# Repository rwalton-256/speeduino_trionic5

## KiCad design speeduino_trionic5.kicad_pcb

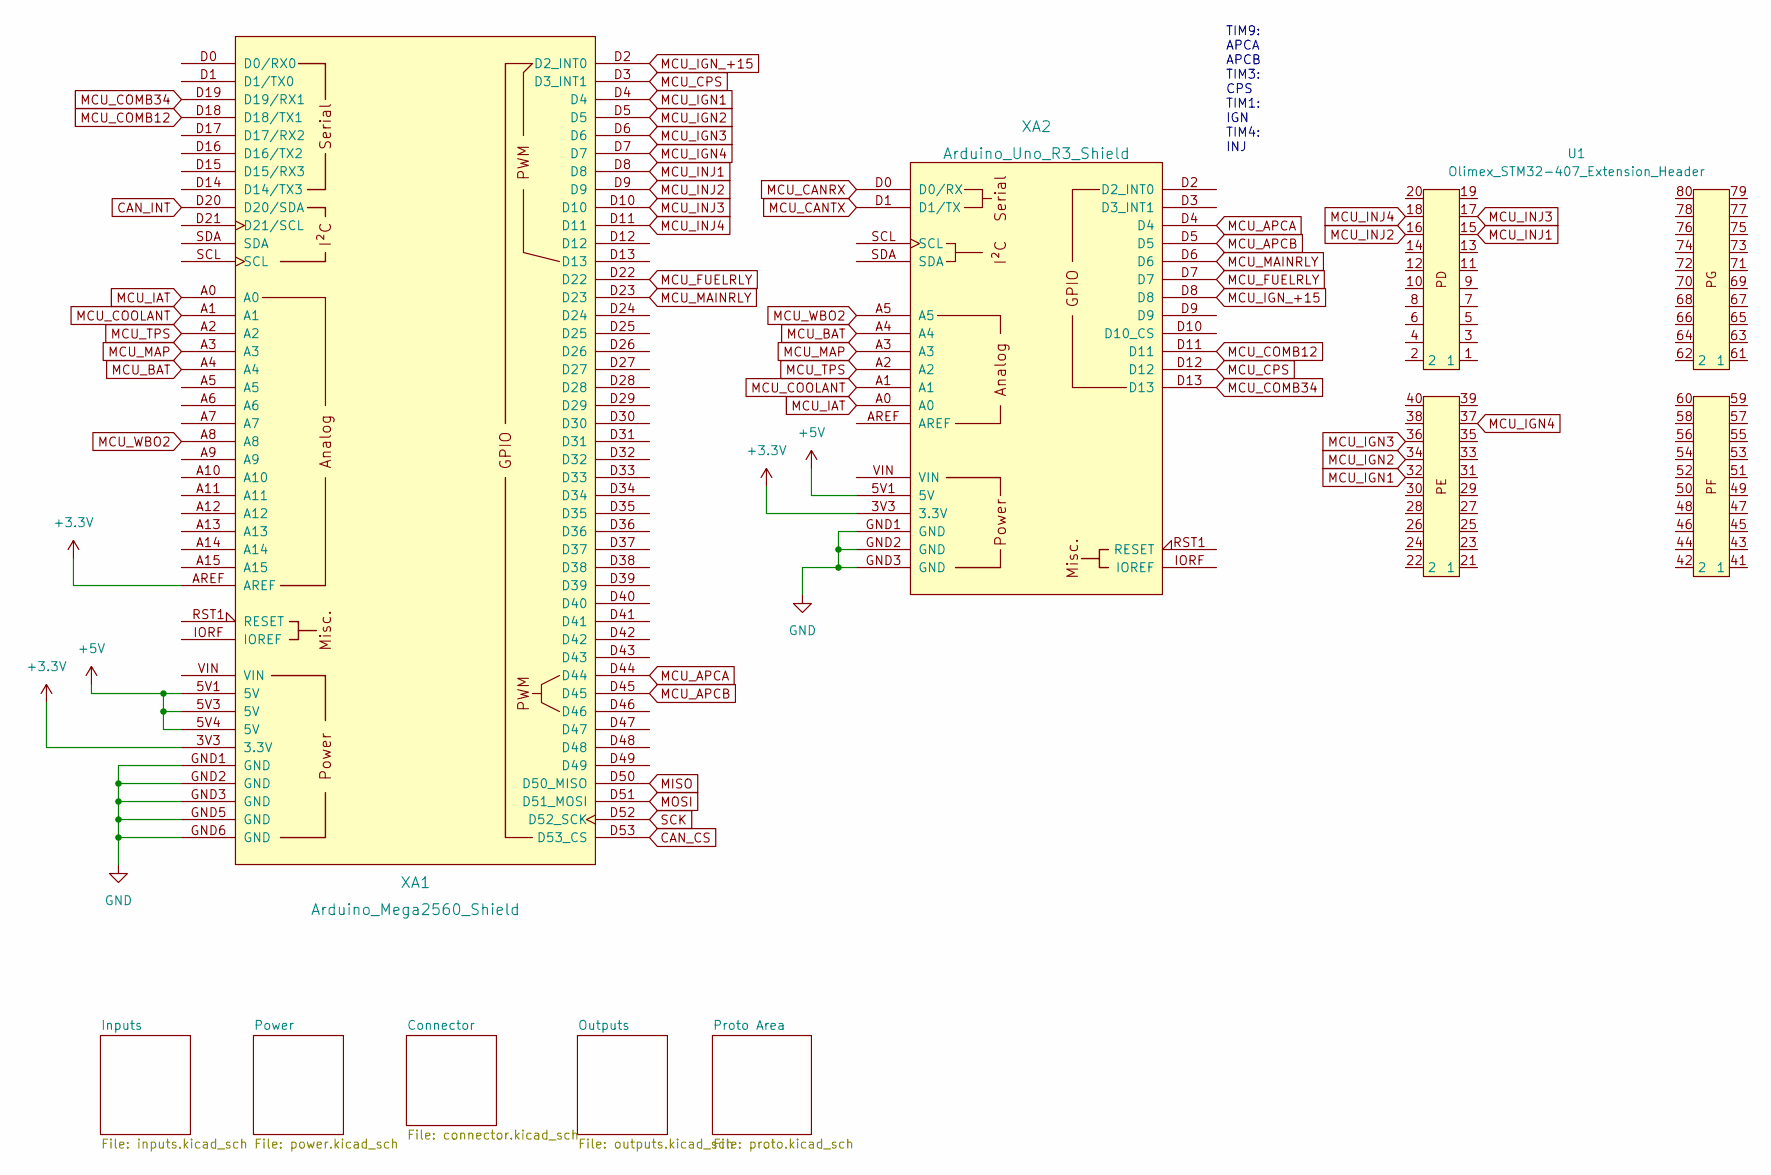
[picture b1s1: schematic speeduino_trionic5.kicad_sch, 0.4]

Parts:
U1: Olimex_STM32-407_Extension_Header; Olimex_STM32-E407_Extenstion_Header
XA1: Arduino_Mega2560_Shield
XA2: Arduino_Uno_R3_Shield

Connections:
+3.3V: XA1.3V3 (3.3V), XA1.AREF, XA2.3V3 (3.3V); also elsewhere on the board
+5V: XA1.5V1 (5V), XA1.5V3 (5V), XA1.5V4 (5V), XA2.5V1 (5V); also elsewhere on the board
CAN_CS: XA1.D53 (D53_CS); also elsewhere on the board
CAN_INT: XA1.D20 (D20/SDA); also elsewhere on the board
GND: XA1.GND1 (GND), XA1.GND2 (GND), XA1.GND3 (GND), XA1.GND5 (GND), XA1.GND6 (GND), XA2.GND1 (GND), XA2.GND2 (GND), XA2.GND3 (GND); also elsewhere on the board
MCU_APCA: XA1.D44, XA2.D4; also elsewhere on the board
MCU_APCB: XA1.D45, XA2.D5; also elsewhere on the board
MCU_BAT: XA1.A4, XA2.A4; also elsewhere on the board
MCU_CANRX: XA2.D0 (D0/RX); also elsewhere on the board
MCU_CANTX: XA2.D1 (D1/TX); also elsewhere on the board
MCU_COMB12: XA1.D18 (D18/TX1), XA2.D11; also elsewhere on the board
MCU_COMB34: XA1.D19 (D19/RX1), XA2.D13; also elsewhere on the board
MCU_COOLANT: XA1.A1, XA2.A1; also elsewhere on the board
MCU_CPS: XA1.D3 (D3_INT1), XA2.D12; also elsewhere on the board
MCU_FUELRLY: XA1.D22, XA2.D7; also elsewhere on the board
MCU_IAT: XA1.A0, XA2.A0; also elsewhere on the board
MCU_IGN1: U1.32, XA1.D4; also elsewhere on the board
MCU_IGN2: U1.34, XA1.D5; also elsewhere on the board
MCU_IGN3: U1.36, XA1.D6; also elsewhere on the board
MCU_IGN4: U1.37, XA1.D7; also elsewhere on the board
MCU_IGN_+15: XA1.D2 (D2_INT0), XA2.D8; also elsewhere on the board
MCU_INJ1: U1.15, XA1.D8; also elsewhere on the board
MCU_INJ2: U1.16, XA1.D9; also elsewhere on the board
MCU_INJ3: U1.17, XA1.D10; also elsewhere on the board
MCU_INJ4: U1.18, XA1.D11; also elsewhere on the board
MCU_MAINRLY: XA1.D23, XA2.D6; also elsewhere on the board
MCU_MAP: XA1.A3, XA2.A3; also elsewhere on the board
MCU_TPS: XA1.A2, XA2.A2; also elsewhere on the board
MCU_WBO2: XA1.A8, XA2.A5; also elsewhere on the board
MISO: XA1.D50 (D50_MISO); also elsewhere on the board
MOSI: XA1.D51 (D51_MOSI); also elsewhere on the board
SCK: XA1.D52 (D52_SCK); also elsewhere on the board

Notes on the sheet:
TIM9: APCA APCB TIM3: CPS TIM1: IGN TIM4: INJ

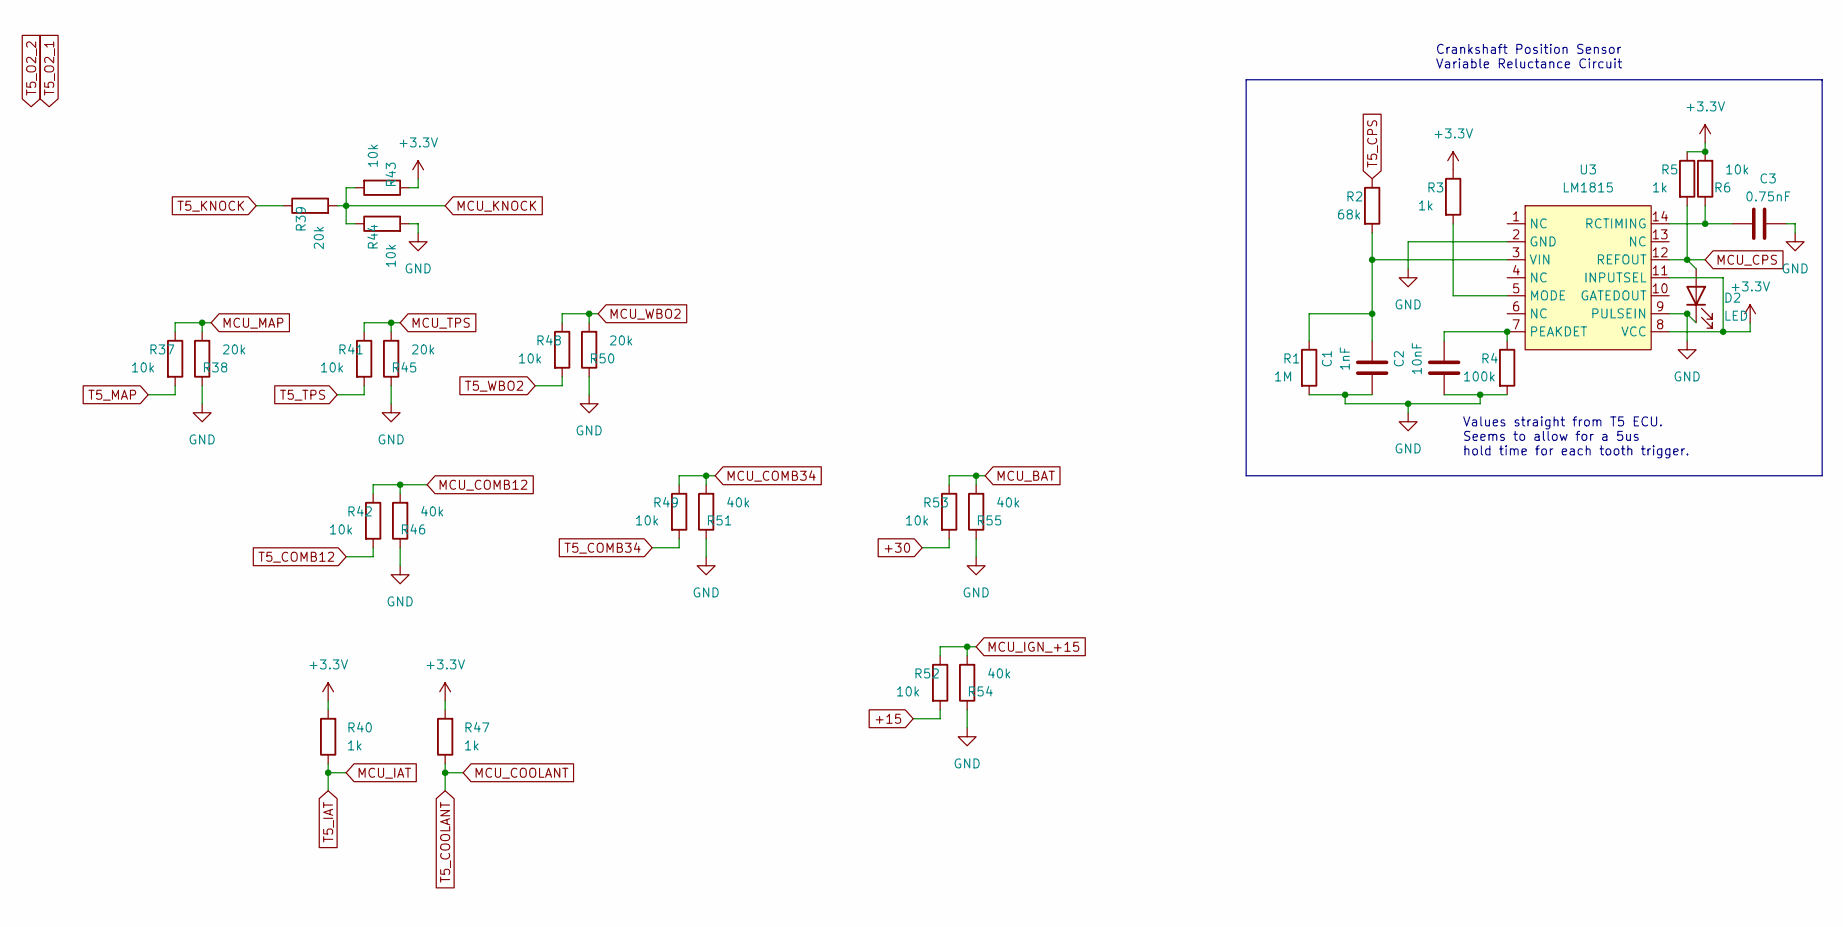
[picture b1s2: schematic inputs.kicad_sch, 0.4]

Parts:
C1: 1nF; C_0603_1608Metric; JLCPCB C296015
C2: 10nF; C_0603_1608Metric; JLCPCB C424843
C3: 0.75nF; C_0603_1608Metric; JLCPCB C576855
D2: LED; LED_0603_1608Metric; JLCPCB C84263
R1: 1M; R_0603_1608Metric; JLCPCB C188125
R2: 68k; R_0603_1608Metric; JLCPCB C2933251
R3, R5, R40, R47: 1k; R_0603_1608Metric; JLCPCB C217840
R4: 100k; R_0603_1608Metric; JLCPCB C100822
R6, R37, R41, R42, R43, R44, R48, R49, R52, R53: 10k; R_0603_1608Metric; JLCPCB C21190
R38, R39, R45, R50: 20k; R_0603_1608Metric; JLCPCB C2924194
R46, R51, R54, R55: 40k; R_0603_1608Metric; JLCPCB C706088
U3: LM1815; SOIC-14_3.9x8.7mm_P1.27mm

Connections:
+3.3V: R3.1, R5.1, R6.2, R40.2, R43.1, R47.2, U3.8 (VCC), U3.11 (INPUTSEL); also elsewhere on the board
+15: R52.2; also elsewhere on the board
+30: R53.2; also elsewhere on the board
GND: C1.1, C2.1, C3.2, D2.1 (K), R1.2, R4.2, R38.1, R44.2, R45.1, R46.1, R50.1, R51.1, R54.1, R55.1, U3.2 (GND), U3.9 (PULSEIN); also elsewhere on the board
MCU_BAT: R53.1, R55.2; also elsewhere on the board
MCU_COMB12: R42.1, R46.2; also elsewhere on the board
MCU_COMB34: R49.1, R51.2; also elsewhere on the board
MCU_COOLANT: R47.1; also elsewhere on the board
MCU_CPS: D2.2 (A), R5.2, U3.12 (REFOUT); also elsewhere on the board
MCU_IAT: R40.1; also elsewhere on the board
MCU_IGN_+15: R52.1, R54.2; also elsewhere on the board
MCU_KNOCK: R39.2, R43.2, R44.1
MCU_MAP: R37.1, R38.2; also elsewhere on the board
MCU_TPS: R41.1, R45.2; also elsewhere on the board
MCU_WBO2: R48.1, R50.2; also elsewhere on the board
unnamed: C1.2, R1.1, R2.2, U3.3 (VIN)
unnamed: C2.2, R4.1, U3.7 (PEAKDET)
unnamed: C3.1, R6.1, U3.14 (RCTIMING)
unnamed: R3.2, U3.5 (MODE)
T5_COMB12: R42.2; also elsewhere on the board
T5_COMB34: R49.2; also elsewhere on the board
T5_CPS: R2.1; also elsewhere on the board
T5_KNOCK: R39.1; also elsewhere on the board
T5_MAP: R37.2; also elsewhere on the board
T5_TPS: R41.2; also elsewhere on the board
T5_WBO2: R48.2; also elsewhere on the board

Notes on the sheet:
Crankshaft Position Sensor Variable Reluctance Circuit
Values straight from T5 ECU. Seems to allow for a 5us hold time for each tooth trigger.

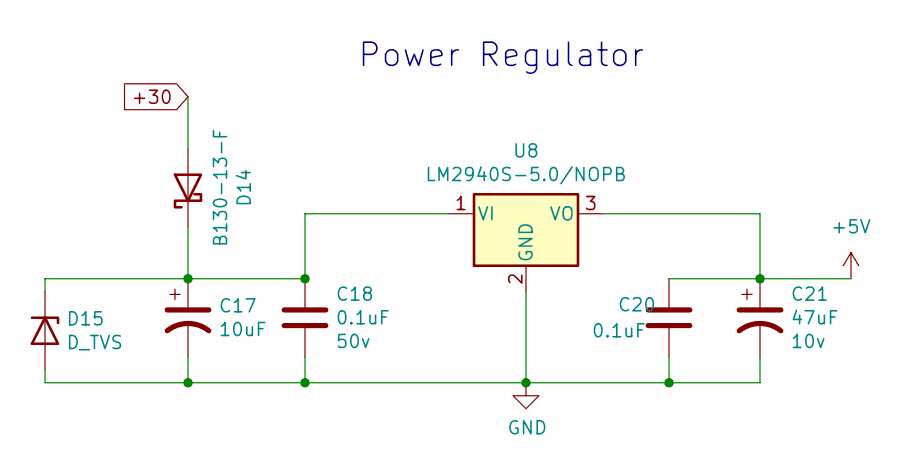
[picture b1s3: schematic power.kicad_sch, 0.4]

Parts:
C17: 10uF; CP_EIA-7343-31_Kemet-D; Voltage 35v; Manufacturer_Part_Number T491D106K050AT; Digikey Part Number 399-8361-1-ND
C18: 0.1uF; C_0805_2012Metric; Voltage 50v; Manufacturer_Part_Number CC0805KRX7R9BB104; Digikey Part Number 311-1140-1-ND
C20: 0.1uF; C_0805_2012Metric; Manufacturer_Part_Number CC0805KRX7R9BB104; Digikey Part Number 311-1140-1-ND
C21: 47uF; CP_EIA-3528-21_Kemet-B; Voltage 10v; Manufacturer_Part_Number TAJB476K006RNJ; Digikey Part Number 478-1692-1-ND
D14: B130-13-F; D_SMA; Manufacturer_Part_Number B130-13-F; Digikey Part Number B130-FDICT-ND
D15: D_TVS; D_SMB; Manufacturer_Part_Number SMBJ40A-Q; Digikey Part Number SMBJ40A-QCT-ND
U8: LM2940S-5.0/NOPB; SOT-223; Manufacturer_Part_Number LM2940S-5.0/NOPB; Digikey Part Number LM2940S-5.0/NOPB-ND

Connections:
+5V: C20.1, C21.1, U8.3 (VO); also elsewhere on the board
+30: D14.2 (A); also elsewhere on the board
GND: C17.2, C18.2, C20.2, C21.2, D15.2 (A), U8.2 (GND); also elsewhere on the board
unnamed: C17.1, C18.1, D14.1 (K), D15.1 (K), U8.1 (VI)

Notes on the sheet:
Power Regulator

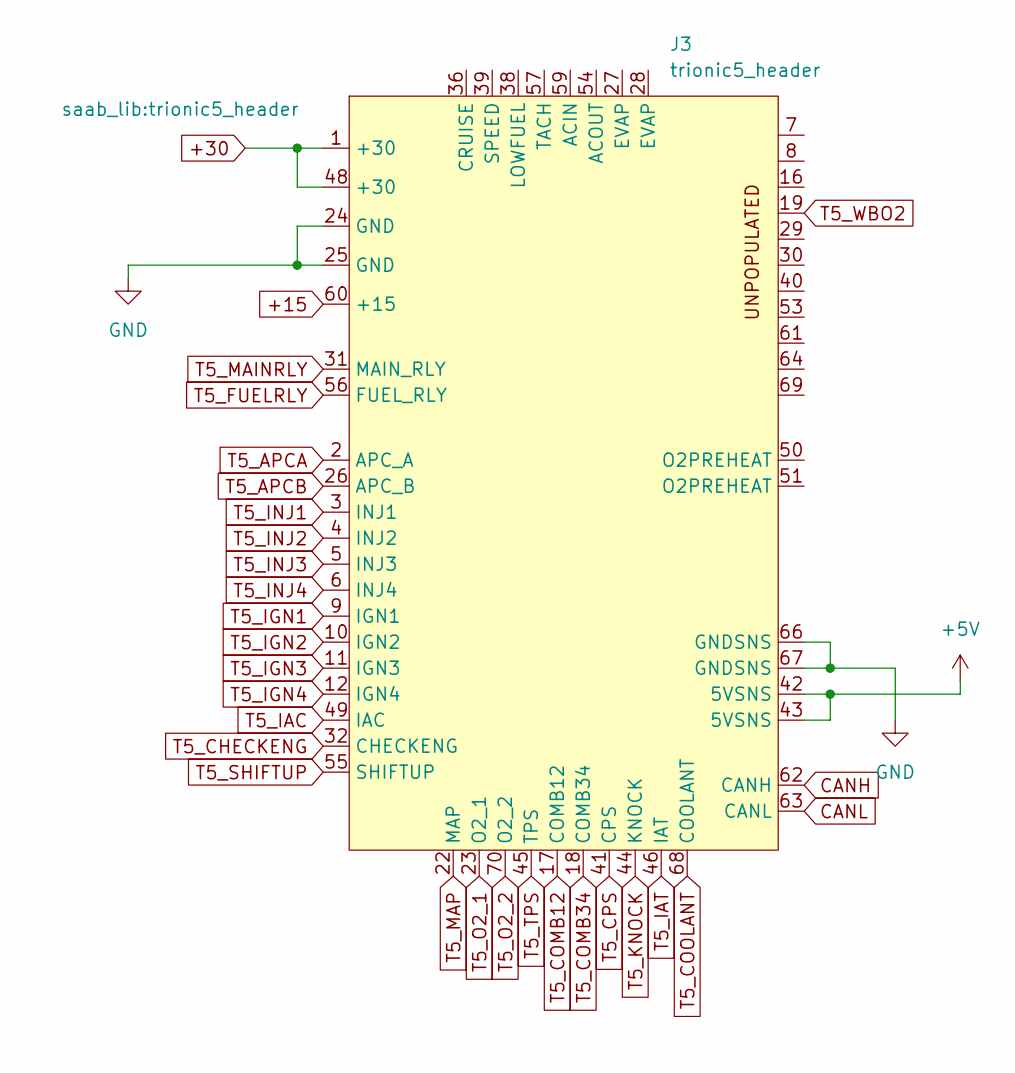
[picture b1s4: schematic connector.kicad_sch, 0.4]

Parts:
J3: trionic5_header

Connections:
+5V: J3.42 (5VSNS), J3.43 (5VSNS); also elsewhere on the board
+15: J3.60 (+15); also elsewhere on the board
+30: J3.1 (+30), J3.48 (+30); also elsewhere on the board
CANH: J3.62 (CANH); also elsewhere on the board
CANL: J3.63 (CANL); also elsewhere on the board
GND: J3.24 (GND), J3.25 (GND), J3.66 (GNDSNS), J3.67 (GNDSNS); also elsewhere on the board
MCU_COOLANT: J3.68 (COOLANT); also elsewhere on the board
MCU_IAT: J3.46 (IAT); also elsewhere on the board
T5_APCA: J3.2 (APC_A); also elsewhere on the board
T5_APCB: J3.26 (APC_B); also elsewhere on the board
T5_CHECKENG: J3.32 (CHECKENG); also elsewhere on the board
T5_COMB12: J3.17 (COMB12); also elsewhere on the board
T5_COMB34: J3.18 (COMB34); also elsewhere on the board
T5_CPS: J3.41 (CPS); also elsewhere on the board
T5_FUELRLY: J3.56 (FUEL_RLY); also elsewhere on the board
T5_IAC: J3.49 (IAC); also elsewhere on the board
T5_IGN1: J3.9 (IGN1); also elsewhere on the board
T5_IGN2: J3.10 (IGN2); also elsewhere on the board
T5_IGN3: J3.11 (IGN3); also elsewhere on the board
T5_IGN4: J3.12 (IGN4); also elsewhere on the board
T5_INJ1: J3.3 (INJ1); also elsewhere on the board
T5_INJ2: J3.4 (INJ2); also elsewhere on the board
T5_INJ3: J3.5 (INJ3); also elsewhere on the board
T5_INJ4: J3.6 (INJ4); also elsewhere on the board
T5_KNOCK: J3.44 (KNOCK); also elsewhere on the board
T5_MAINRLY: J3.31 (MAIN_RLY); also elsewhere on the board
T5_MAP: J3.22 (MAP); also elsewhere on the board
T5_O2_1: J3.23 (O2_1)
T5_O2_2: J3.70 (O2_2)
T5_SHIFTUP: J3.55 (SHIFTUP); also elsewhere on the board
T5_TPS: J3.45 (TPS); also elsewhere on the board
T5_WBO2: J3.19; also elsewhere on the board

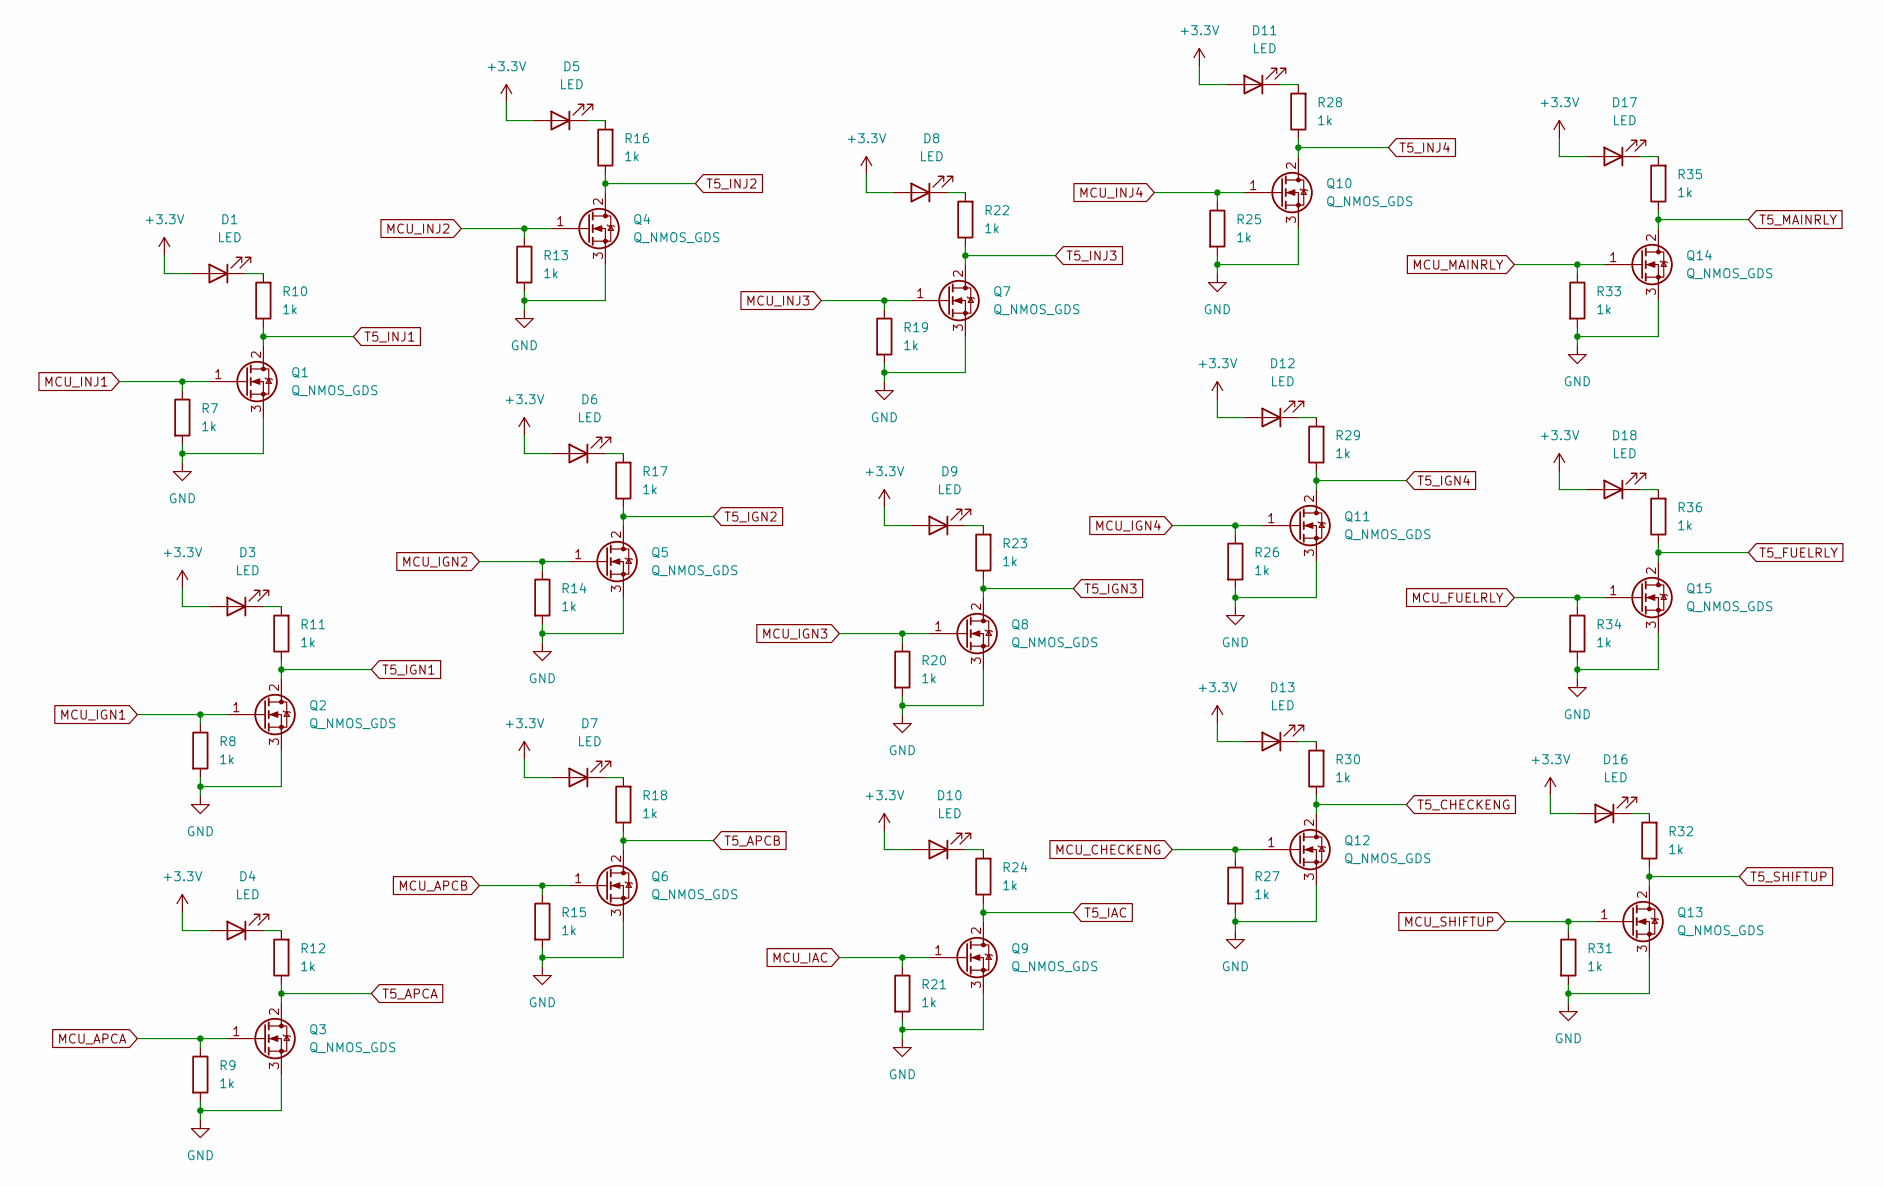
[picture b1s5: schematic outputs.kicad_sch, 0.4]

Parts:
D1, D3, D4, D5, D6, D7, D8, D9, D10, D11, D12, D13, D16, D17, D18: LED; LED_0603_1608Metric; JLCPCB C84263
Q1, Q2, Q3, Q4, Q5, Q6, Q7, Q8, Q9, Q10, Q11, Q12, Q13, Q14, Q15: Q_NMOS_GDS; TO-252-2; JLCPCB C396090
R7, R8, R9, R10, R11, R12, R13, R14, R15, R16, R17, R18, R19, R20, R21, R22, R23, R24, R25, R26, R27, R28, R29, R30, R31, R32, R33, R34, R35, R36: 1k; R_0603_1608Metric; JLCPCB C217840

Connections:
+3.3V: D1.2 (A), D3.2 (A), D4.2 (A), D5.2 (A), D6.2 (A), D7.2 (A), D8.2 (A), D9.2 (A), D10.2 (A), D11.2 (A), D12.2 (A), D13.2 (A), D16.2 (A), D17.2 (A), D18.2 (A); also elsewhere on the board
GND: Q1.3 (S), Q2.3 (S), Q3.3 (S), Q4.3 (S), Q5.3 (S), Q6.3 (S), Q7.3 (S), Q8.3 (S), Q9.3 (S), Q10.3 (S), Q11.3 (S), Q12.3 (S), Q13.3 (S), Q14.3 (S), Q15.3 (S), R7.2, R8.2, R9.2, R13.2, R14.2, R15.2, R19.2, R20.2, R21.2, R25.2, R26.2, R27.2, R31.2, R33.2, R34.2; also elsewhere on the board
MCU_APCA: Q3.1 (G), R9.1; also elsewhere on the board
MCU_APCB: Q6.1 (G), R15.1; also elsewhere on the board
MCU_CHECKENG: Q12.1 (G), R27.1
MCU_FUELRLY: Q15.1 (G), R34.1; also elsewhere on the board
MCU_IAC: Q9.1 (G), R21.1
MCU_IGN1: Q2.1 (G), R8.1; also elsewhere on the board
MCU_IGN2: Q5.1 (G), R14.1; also elsewhere on the board
MCU_IGN3: Q8.1 (G), R20.1; also elsewhere on the board
MCU_IGN4: Q11.1 (G), R26.1; also elsewhere on the board
MCU_INJ1: Q1.1 (G), R7.1; also elsewhere on the board
MCU_INJ2: Q4.1 (G), R13.1; also elsewhere on the board
MCU_INJ3: Q7.1 (G), R19.1; also elsewhere on the board
MCU_INJ4: Q10.1 (G), R25.1; also elsewhere on the board
MCU_MAINRLY: Q14.1 (G), R33.1; also elsewhere on the board
MCU_SHIFTUP: Q13.1 (G), R31.1
unnamed: D1.1 (K), R10.2
unnamed: D3.1 (K), R11.2
unnamed: D4.1 (K), R12.2
unnamed: D5.1 (K), R16.2
unnamed: D6.1 (K), R17.2
unnamed: D7.1 (K), R18.2
unnamed: D8.1 (K), R22.2
unnamed: D9.1 (K), R23.2
unnamed: D10.1 (K), R24.2
unnamed: D11.1 (K), R28.2
unnamed: D12.1 (K), R29.2
unnamed: D13.1 (K), R30.2
unnamed: D16.1 (K), R32.2
unnamed: D17.1 (K), R35.2
unnamed: D18.1 (K), R36.2
T5_APCA: Q3.2 (D), R12.1; also elsewhere on the board
T5_APCB: Q6.2 (D), R18.1; also elsewhere on the board
T5_CHECKENG: Q12.2 (D), R30.1; also elsewhere on the board
T5_FUELRLY: Q15.2 (D), R36.1; also elsewhere on the board
T5_IAC: Q9.2 (D), R24.1; also elsewhere on the board
T5_IGN1: Q2.2 (D), R11.1; also elsewhere on the board
T5_IGN2: Q5.2 (D), R17.1; also elsewhere on the board
T5_IGN3: Q8.2 (D), R23.1; also elsewhere on the board
T5_IGN4: Q11.2 (D), R29.1; also elsewhere on the board
T5_INJ1: Q1.2 (D), R10.1; also elsewhere on the board
T5_INJ2: Q4.2 (D), R16.1; also elsewhere on the board
T5_INJ3: Q7.2 (D), R22.1; also elsewhere on the board
T5_INJ4: Q10.2 (D), R28.1; also elsewhere on the board
T5_MAINRLY: Q14.2 (D), R35.1; also elsewhere on the board
T5_SHIFTUP: Q13.2 (D), R32.1; also elsewhere on the board

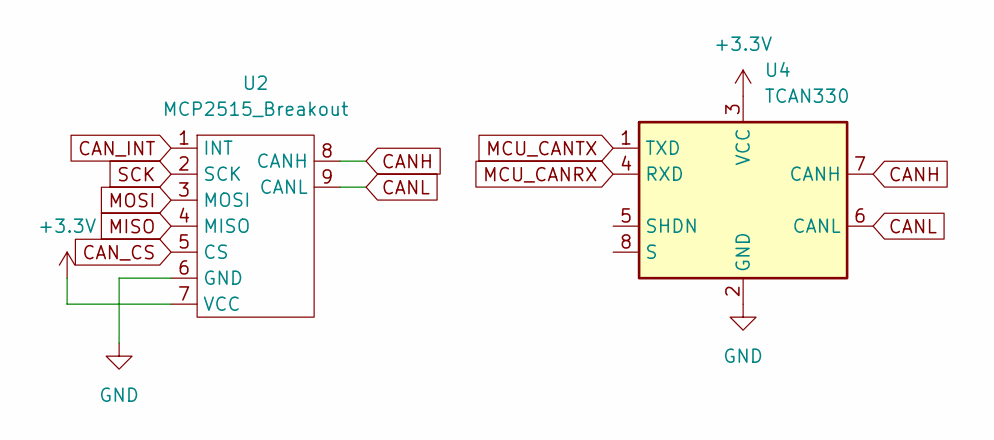
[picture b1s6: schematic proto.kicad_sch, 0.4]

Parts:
U2: MCP2515_Breakout
U4: TCAN330; SOT-23-8; JLCPCB C2877587

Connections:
+3.3V: U2.7 (VCC), U4.3 (VCC); also elsewhere on the board
CANH: U2.8 (CANH), U4.7 (CANH); also elsewhere on the board
CANL: U2.9 (CANL), U4.6 (CANL); also elsewhere on the board
CAN_CS: U2.5 (CS); also elsewhere on the board
CAN_INT: U2.1 (INT); also elsewhere on the board
GND: U2.6 (GND), U4.2 (GND); also elsewhere on the board
MCU_CANRX: U4.4 (RXD); also elsewhere on the board
MCU_CANTX: U4.1 (TXD); also elsewhere on the board
MISO: U2.4 (MISO); also elsewhere on the board
MOSI: U2.3 (MOSI); also elsewhere on the board
SCK: U2.2 (SCK); also elsewhere on the board

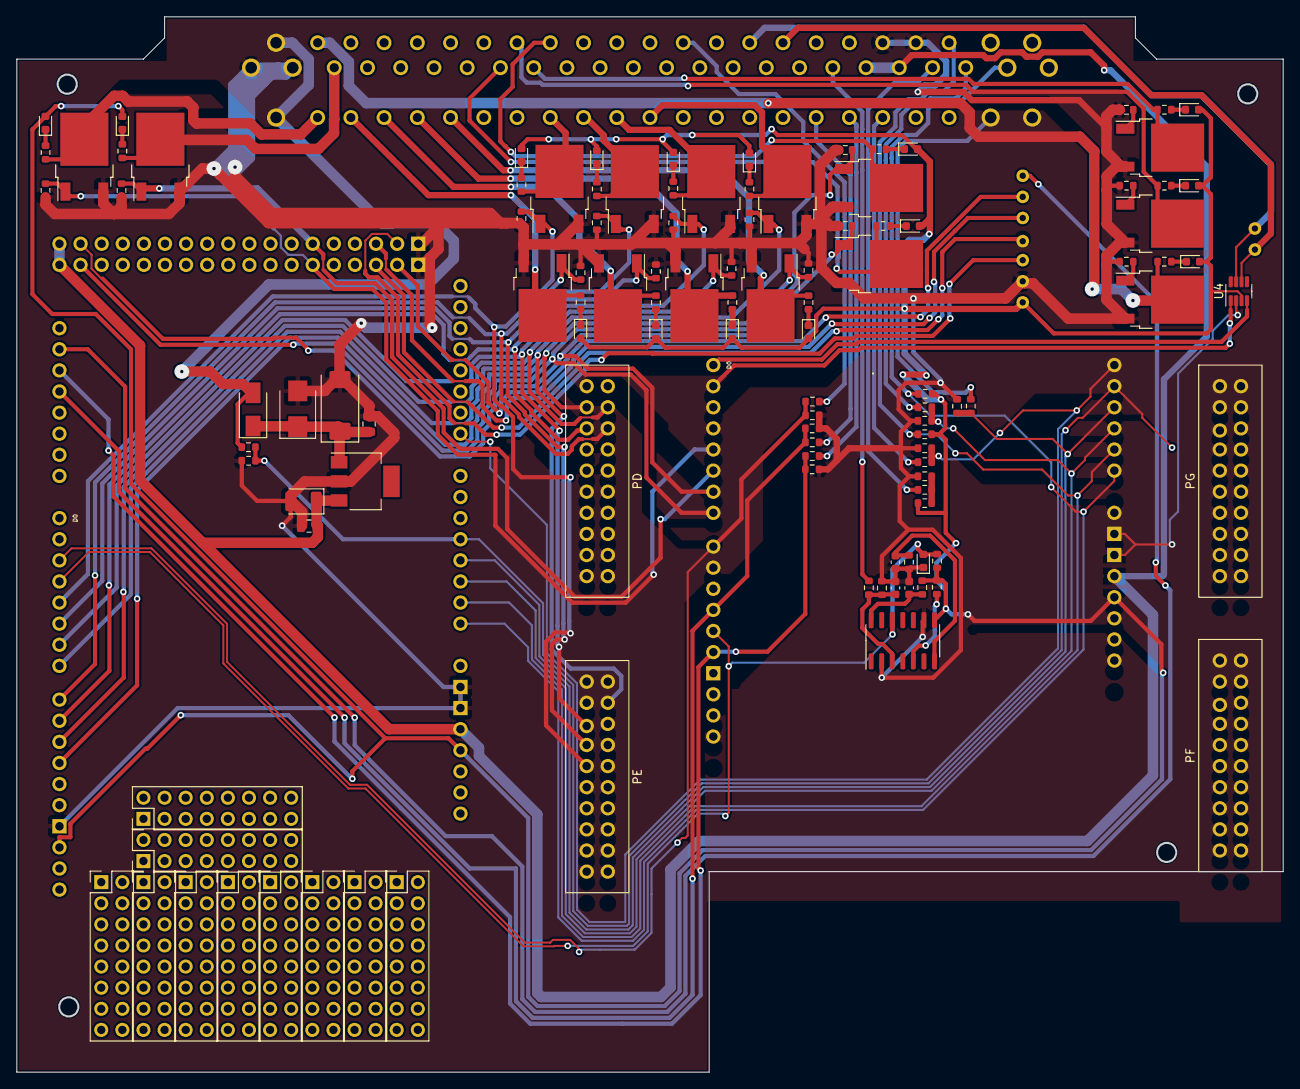
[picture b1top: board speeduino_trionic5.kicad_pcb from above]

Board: 2 copper layers, 152.4 x 127.0 mm, 103 parts (1 on the bottom side), 82 nets.

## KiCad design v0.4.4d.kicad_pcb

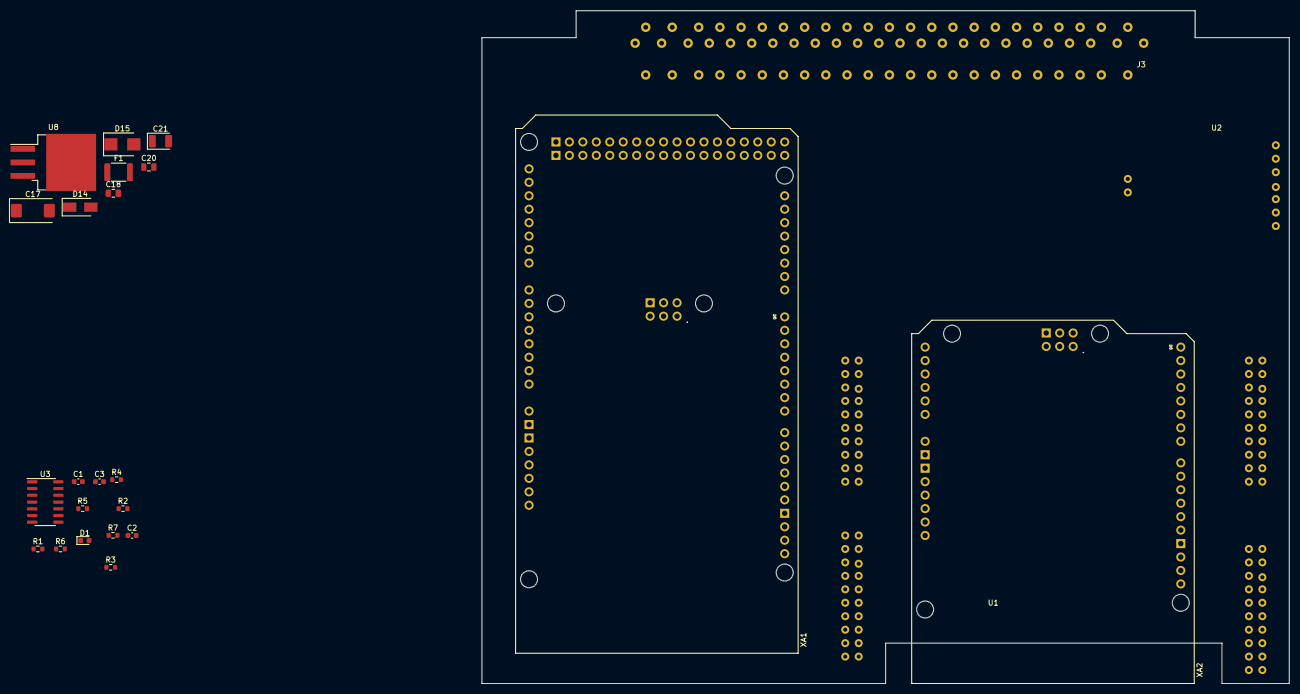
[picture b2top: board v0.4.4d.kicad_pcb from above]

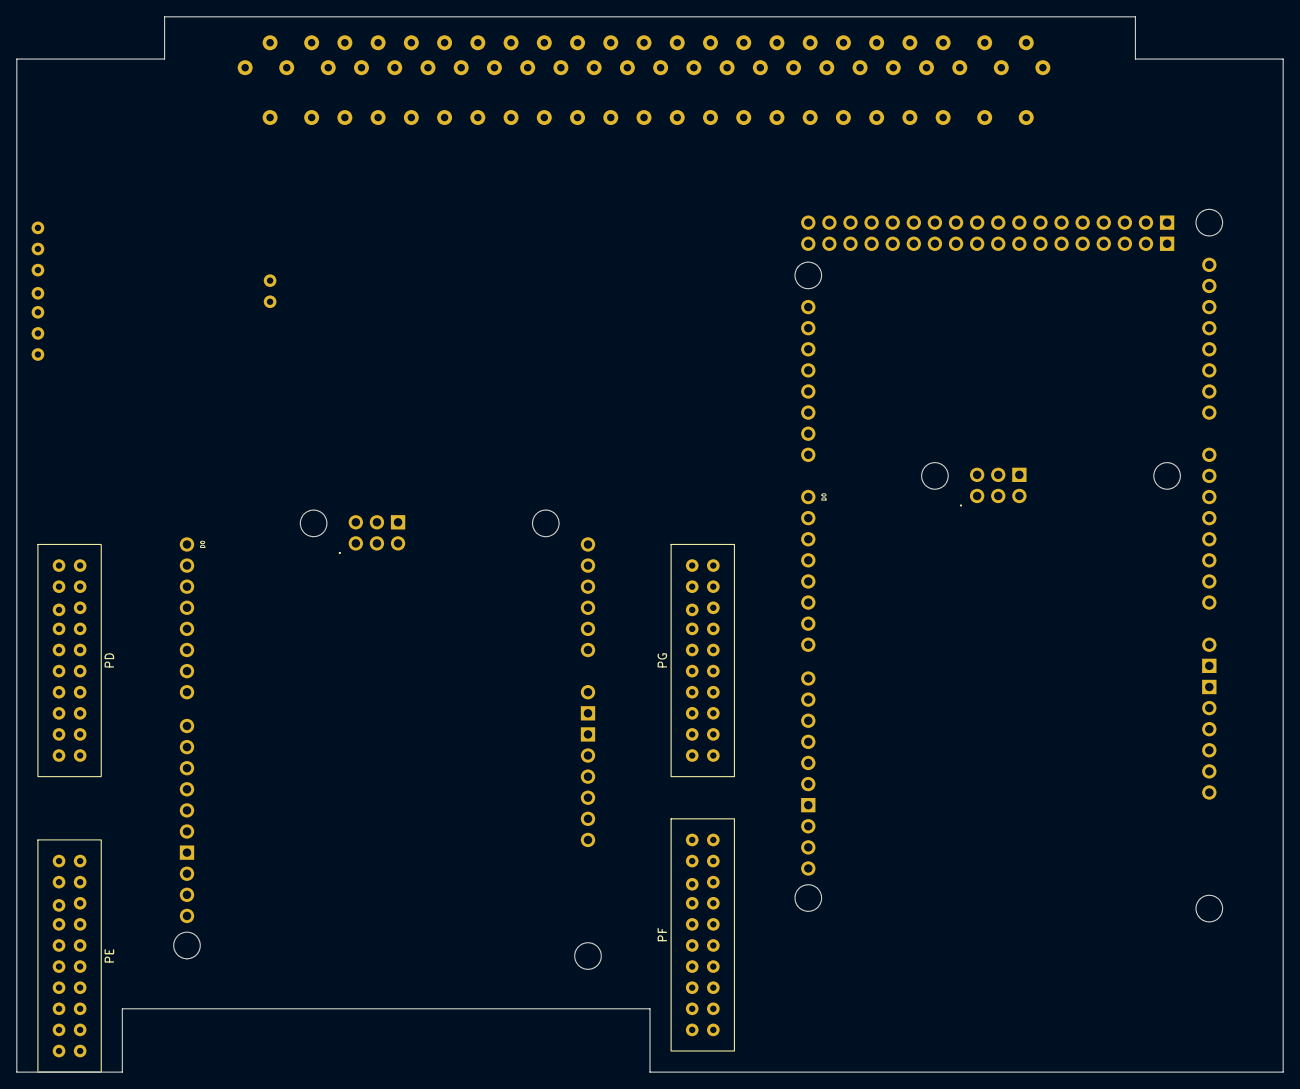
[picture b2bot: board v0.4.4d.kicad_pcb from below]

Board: 2 copper layers, 152.4 x 127.0 mm, 25 parts (4 on the bottom side), 12 nets, no tracks yet.

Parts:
C1: 1nF; C_0603_1608Metric
C2: 10nF; C_0603_1608Metric
C3: 0.75nF; C_0603_1608Metric
C17: 10uF; CP_EIA-7343-31_Kemet-D
C18, C20: 0.1uF; C_0805_2012Metric
C21: 47uF; CP_EIA-3528-21_Kemet-B
D1: LED; LED_0603_1608Metric
D14: B130-13-F; D_SMA
D15: D_TVS; D_SMB
F1: Polyfuse; Fuse_1812_4532Metric
J3: trionic5_header
R1: 1M; R_0603_1608Metric
R2: 68k; R_0603_1608Metric
R3, R7: 1k; R_0603_1608Metric
R4: 100k; R_0603_1608Metric
R5, R6: 10k; R_0603_1608Metric
U1: Olimex_STM32-407_Extension_Header; Olimex_STM32-E407_Extenstion_Header
U2: MCP2515_Breakout
U3: LM1815; SOIC-14_3.9x8.7mm_P1.27mm
U8: LM2940S-5.0/NOPB; TO-263-3_TabPin2
XA1: Arduino_Mega2560_Shield
XA2: Arduino_Uno_R3_Shield

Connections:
+3.3V: D1.2 (A), R3.1, R5.1, R6.1, U3.8 (VCC), U3.11 (INPUTSEL)
CANH: J3.62 (CANH), U2.8 (CANH)
CANL: J3.63 (CANL), U2.9 (CANL)
GND: C1.1, C2.1, C3.2, C17.2, C18.2, C20.2, C21.2, D15.2 (A), R1.2, R4.2, U3.2 (GND), U3.9 (PULSEIN), U8.2 (GND)
MCU_CPS: R5.2, R7.1, U3.12 (REFOUT), XA1.D3 (D3_INT1)
unnamed: C1.2, R1.1, R2.2, U3.3 (VIN)
unnamed: C2.2, R4.1, U3.7 (PEAKDET)
unnamed: C3.1, R6.2, U3.14 (RCTIMING)
unnamed: D1.1 (K), R7.2
unnamed: R3.2, U3.5 (MODE)
VDD: C20.1, C21.1, F1.2, U8.3 (VO)
VRegIn: C17.1, C18.1, D14.1 (K), D15.1 (K), U8.1 (VI)

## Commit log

2023-07-05 Trying to rename
2023-07-09 Boards should be placed correctly now
2023-07-15 Low side drivers mostly in order
2023-07-16 Add JLCPCB Components
2023-07-16 More changes
2023-07-16 Add stuff
2023-07-16 Fix submodule
2023-07-17 Basically done!
2023-07-17 Added solderable breadboard area
2023-07-17 Add copper pour and remove fuel ign tab
